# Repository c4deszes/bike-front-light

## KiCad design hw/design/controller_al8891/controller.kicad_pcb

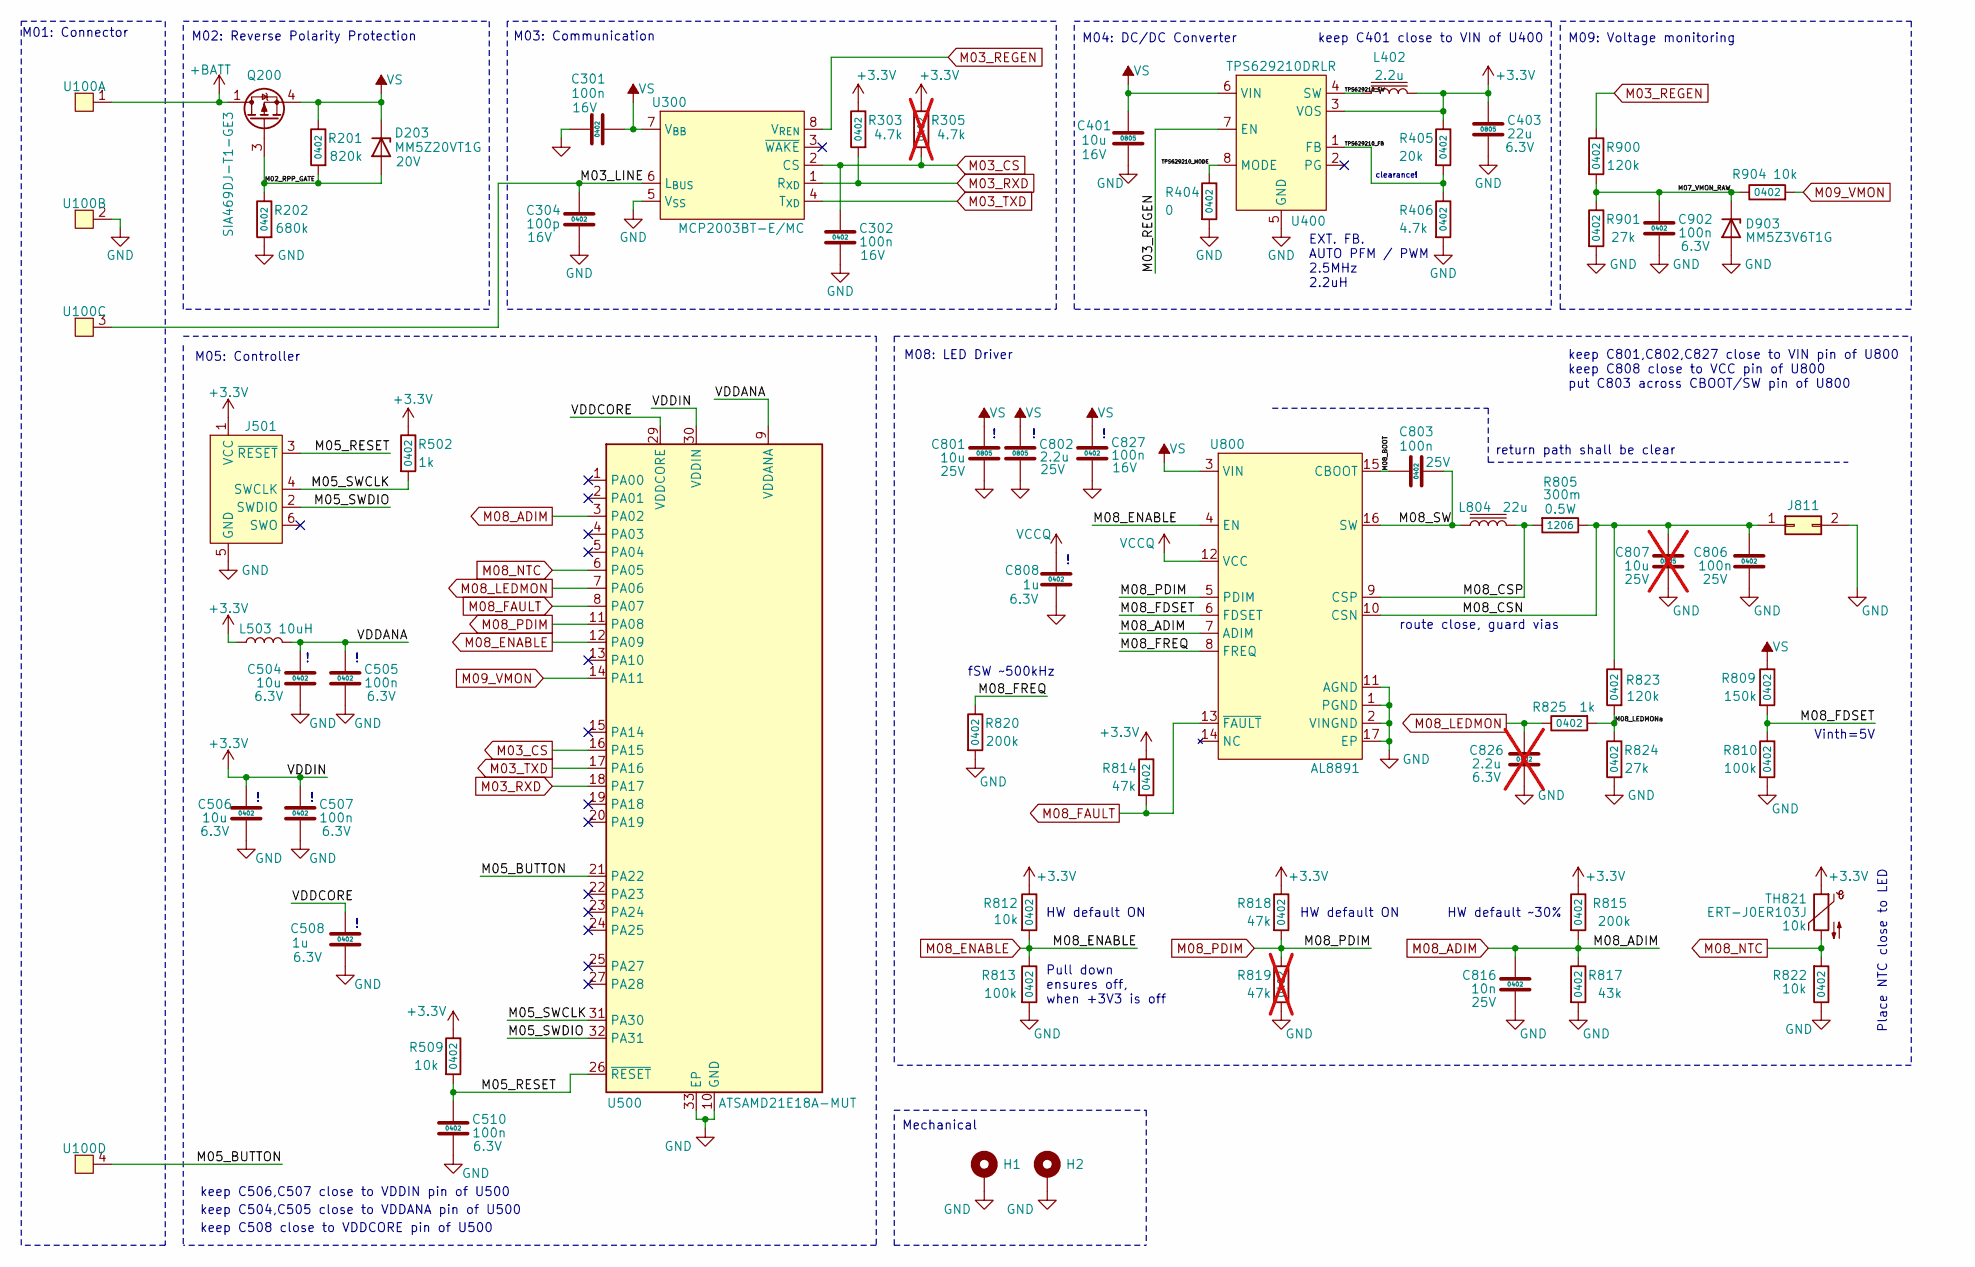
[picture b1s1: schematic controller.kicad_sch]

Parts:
C301, C302, C827: 100n; C_0402_1005Metric; Rating 16V
C304: 100p; C_0402_1005Metric; Rating 16V
C401: 10u; C_0805_2012Metric; Rating 16V
C403: 22u; C_0805_2012Metric; Rating 6.3V
C504, C506: 10u; C_0402_1005Metric; Rating 6.3V
C505, C507, C510, C902: 100n; C_0402_1005Metric; Rating 6.3V
C508, C808: 1u; C_0402_1005Metric; Rating 6.3V
C801: 10u; C_0805_2012Metric; Rating 25V
C802: 2.2u; C_0805_2012Metric; Rating 25V
C803: 100n; C_0603_1608Metric; Rating 25V
C806: 100n; C_0402_1005Metric; Rating 25V
C807: 10u; C_0805_2012Metric; Rating 25V; not fitted
C816: 10n; C_0402_1005Metric; Rating 25V
C826: 2.2u; C_0402_1005Metric; Rating 6.3V; not fitted
D203: MM5Z20VT1G; D_SOD-523; Rating 20V
D903: MM5Z3V6T1G; D_SOD-523
H1, H2: MountingHole_Pad; MountingHole_2.2mm_M2_DIN965_Pad_TopOnly
J501: Conn_ARM_SWD_TagConnect_TC2030-NL; Tag-Connect_TC2030-IDC-NL_2x03_P1.27mm_Vertical
J811: Conn_02x01; 2pinConnector
L402: 2.2u; L_Coilcraft_LPS3010
L503: 10uH; L_0603_1608Metric
L804: 22u; ASPI-6045
Q200: SIA469DJ-T1-GE3; Vishay_PowerPAK_SC70-6L_Single
R201: 820k; R_0402_1005Metric
R202: 680k; R_0402_1005Metric
R303, R406: 4.7k; R_0402_1005Metric
R305: 4.7k; R_0402_1005Metric; not fitted
R404: 0; R_0402_1005Metric
R405: 20k; R_0402_1005Metric
R502, R825: 1k; R_0402_1005Metric
R509, R812, R822, R904: 10k; R_0402_1005Metric
R805: 300m; R_1206_3216Metric; Rating 0.5W
R809: 150k; R_0402_1005Metric
R810, R813: 100k; R_0402_1005Metric
R814, R818: 47k; R_0402_1005Metric
R815, R820: 200k; R_0402_1005Metric
R817: 43k; R_0402_1005Metric
R819: 47k; R_0402_1005Metric; not fitted
R823, R900: 120k; R_0402_1005Metric
R824, R901: 27k; R_0402_1005Metric
TH821: ERT-J0ER103J; R_0402_1005Metric
U100: PinHeader_1x04_P2.54mm_Vertical
U300: MCP2003BT-E/MC; DFN-8-1EP_3x2mm_P0.5mm_EP1.7x1.4mm
U400: TPS629210DRLR; SOT-583-8
U500: ATSAMD21E18A-MUT; VQFN-32-1EP_5x5mm_P0.5mm_EP3.5x3.5mm
U800: AL8891; TSSOP-16-1EP_4.4x5mm_P0.65mm_EP3x3mm

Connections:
+3.3V: C403.1, C506.2, C507.2, J501.1 (VCC), L402.2, L503.1, R303.1, R305.1, R405.1, R502.1, R509.1, R812.1, R814.1, R815.1, R818.1, TH821.1, U400.3 (VOS), U500.30 (VDDIN)
+BATT: Q200.1 (D), U100.1
/M02_RPP_GATE: D203.2 (A), Q200.3 (G), R201.2, R202.1
/M03_LINE: C304.2, U100.3, U300.6 (L_{BUS})
/M05_BUTTON: U100.4, U500.21 (PA22)
/M05_RESET: C510.2, J501.3 (~RESET), R509.2, U500.26 (~RESET)
/M05_SWCLK: J501.4 (SWCLK), R502.2, U500.31 (PA30)
/M05_SWDIO: J501.2 (SWDIO), U500.32 (PA31)
/M07_VMON_RAW: C902.2, D903.1 (K), R900.2, R901.1, R904.1
/M08_BOOT: C803.1, U800.15 (CBOOT)
/M08_CSN: C806.1, C807.2, J811.1, R805.1, R823.1, U800.10 (CSN)
/M08_CSP: L804.2, R805.2, U800.9 (CSP)
/M08_FDSET: R809.2, R810.1, U800.6 (FDSET)
/M08_FREQ: R820.1, U800.8 (FREQ)
/M08_LEDMONa: R823.2, R824.1, R825.2
/M08_SW: C803.2, L804.1, U800.16 (SW)
/TPS629210_FB: R405.2, R406.1, U400.1 (FB)
/TPS629210_MODE: R404.1, U400.8 (MODE)
/TPS629210_SW: L402.1, U400.4 (SW)
/VDDANA: C504.2, C505.2, L503.2, U500.9 (VDDANA)
/VDDCORE: C508.2, U500.29 (VDDCORE)
GND: C301.1, C302.1, C304.1, C401.1, C403.2, C504.1, C505.1, C506.1, C507.1, C508.1, C510.1, C801.1, C802.1, C806.2, C807.1, C808.1, C816.2, C826.1, C827.1, C902.1, D903.2 (A), H1.1, H2.1, J501.5 (GND), J811.2, R202.2, R404.2, R406.2, R810.2, R813.2, R817.2, R819.2, R820.2, R822.1, R824.2, R901.2, U100.2, U300.5 (V_{SS}), U400.5 (GND), U500.10 (GND), U500.28 (GND), U500.33 (EP), U800.1 (PGND), U800.2 (VINGND), U800.11 (AGND), U800.17 (EP)
M03_CS: C302.2, R305.2, U300.2 (CS), U500.16 (PA15)
M03_REGEN: R900.1, U300.8 (V_{REN}), U400.7 (EN)
M03_RXD: R303.2, U300.1 (R_{XD}), U500.18 (PA17)
M03_TXD: U300.4 (T_{XD}), U500.17 (PA16)
M08_ADIM: C816.1, R815.2, R817.1, U500.3 (PA02), U800.7 (ADIM)
M08_ENABLE: R812.2, R813.1, U500.12 (PA09), U800.4 (EN)
M08_FAULT: R814.2, U500.8 (PA07), U800.13 (~FAULT)
M08_LEDMON: C826.2, R825.1, U500.7 (PA06)
M08_NTC: R822.2, TH821.2, U500.6 (PA05)
M08_PDIM: R818.2, R819.1, U500.11 (PA08), U800.5 (PDIM)
M09_VMON: R904.2, U500.14 (PA11)
VCCQ: C808.2, U800.12 (VCC)
VS: C301.2, C401.2, C801.2, C802.2, C827.2, D203.1 (K), Q200.4 (S), R201.1, R809.1, U300.7 (V_{BB}), U400.6 (VIN), U800.3 (VIN)

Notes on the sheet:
route close, guard vias
Pull down ensures off, when +3V3 is off
M09: Voltage monitoring
M04: DC/DC Converter
EXT. FB. AUTO PFM / PWM 2.5MHz 2.2uH
return path shall be clear
keep C504,C505 close to VDDANA pin of U500
M02: Reverse Polarity Protection
keep C801,C802,C827 close to VIN pin of U800 keep C808 close to VCC pin of U800 put C803 across CBOOT/SW pin of U800
keep C508 close to VDDCORE pin of U500
HW default ON
clearance!
Mechanical
keep C506,C507 close to VDDIN pin of U500
Place NTC close to LED
M05: Controller
M03: Communication
M01: Connector
Vinth=5V
keep C401 close to VIN of U400
HW default ~30%
M08: LED Driver
fSW ~500kHz

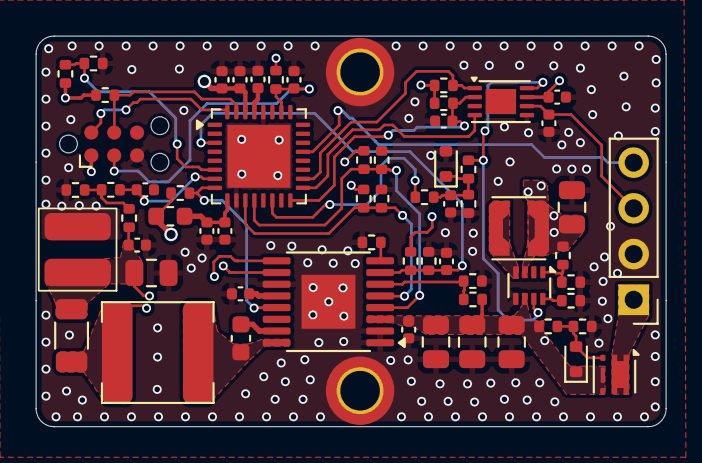
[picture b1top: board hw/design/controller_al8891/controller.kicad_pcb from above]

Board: 4 copper layers, 35.0 x 21.7 mm, 64 parts (0 on the bottom side), 35 nets.

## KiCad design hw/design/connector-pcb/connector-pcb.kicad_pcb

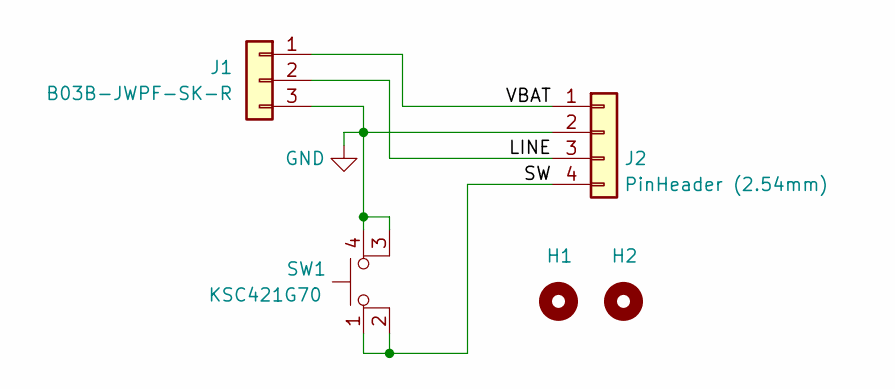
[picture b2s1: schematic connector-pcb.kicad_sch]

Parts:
H1, H2: MountingHole_Pad; MountingHole_2.2mm_M2_ISO14580
J1: B03B-JWPF-SK-R; JST_JWPF_B03B-JWPF-SK-R_1x03_P2.00mm_Vertical
J2: PinHeader (2.54mm); PinHeader_1x04_P2.00mm_Vertical_SMD_Pin1Left
SW1: KSC421G70; KSC4

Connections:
/LINE: J1.2, J2.3
/SW: J2.4, SW1.1, SW1.2
/VBAT: J1.1, J2.1
GND: J1.3, J2.2, SW1.3 (K), SW1.4 (A)

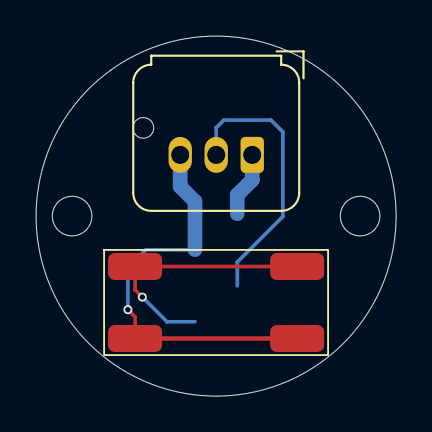
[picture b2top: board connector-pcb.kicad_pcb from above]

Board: 2 copper layers, 20.0 x 20.0 mm, 5 parts (1 on the bottom side), 4 nets.

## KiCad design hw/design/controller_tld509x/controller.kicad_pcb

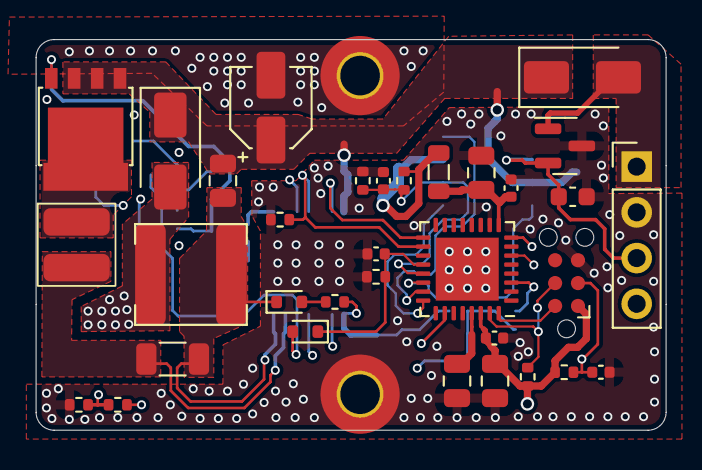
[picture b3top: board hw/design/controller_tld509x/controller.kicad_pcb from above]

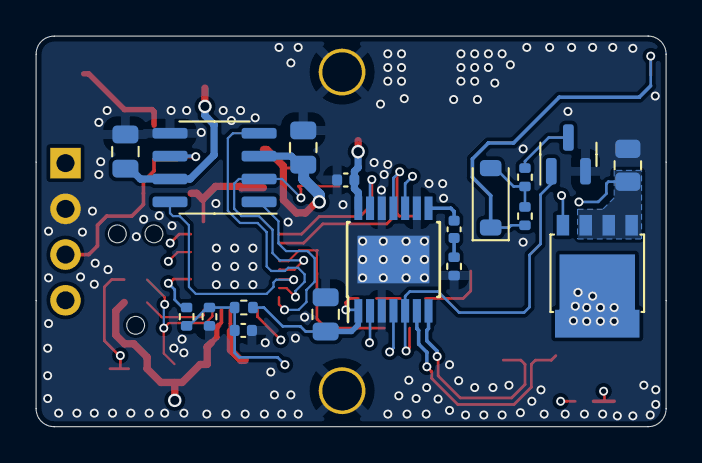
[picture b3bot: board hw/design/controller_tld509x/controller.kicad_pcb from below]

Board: 4 copper layers, 35.0 x 21.7 mm, 53 parts (18 on the bottom side), 35 nets.

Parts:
C300, C401, C403, C502: 10u; C_0805_2012Metric
C301: 22u; C_0805_2012Metric
C302: 220p; C_0603_1608Metric
C303, C400, C402, C404, C501, C504, C506: 100n; C_0402_1005Metric
C405, C503: 2.2u; C_0805_2012Metric
C500: 100u; CP_Elec_4x5.3
C505: 22n; C_0402_1005Metric
D200, D500: SS34F-DC; D_SMA
D300: SDT23C15L02; SOT-23
D501, D502: BAS3005B02; D_SOD-523
D503: BZT52C20-TP; D_SOD-123
H1, H2: M2; MountingHole_2.2mm_M2_Pad_TopOnly
J400: Conn_ARM_SWD_TagConnect_TC2030-NL; Tag-Connect_TC2030-IDC-NL_2x03_P1.27mm_Vertical
J500: Conn_02x01; 2pinConnector
L400: 10uH; L_0805_2012Metric
L500: 15u; ASPI-6045
Q500: BUK6Y24-40PX; LFPAK56
Q501: BUK7Y7R0-40HX; LFPAK56
Q502: 2N7002; SOT-23
R300, R301, R401, R402, R502, R507, R509, R510: 10k; R_0402_1005Metric
R400: 1k; R_0402_1005Metric
R500: 0.430; R_1206_3216Metric
R501: 50m; R_0805_2012Metric
R503, R504, R505, R508: 20k; R_0402_1005Metric
R506: 4.7k; R_0402_1005Metric
TH400: ERT-J0ER103J; R_0402_1005Metric
U100: PinHeader_1x04_P2.54mm_Vertical
U300: MCP2021A-500E/SN; SOIC-8_3.9x4.9mm_P1.27mm
U400: ATSAMC21E18A-MNT; VQFN-32-1EP_5x5mm_P0.5mm_EP3.5x3.5mm
U500: TLD509x; Infineon_PG-TSDSO-14-22

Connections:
+3.3V: C301.1, C403.2, C404.2, J400.1 (VCC), L400.1, R300.1, R400.1, R401.1, TH400.1, U300.3 (VREG), U400.30 (VDDIN)
+BATT: C300.2, C500.1, C501.2, C502.2, D200.1 (K), D500.1 (K), Q500.1 (S), Q500.2 (S), Q500.3 (S), U300.7 (VBB), U500.14 (IN)
/M03_CS: C303.2, R300.2, R301.1, U300.2 (CS/LWAKE), U400.21 (PA22)
/M03_LINE: C302.1, D300.2 (K), U100.3, U300.6 (LBUS)
/M03_RXD: U300.1 (RXD), U400.24 (PA25)
/M03_TXD: U300.4 (TXD), U400.23 (PA24)
/M03_TXE: U300.8 (~FAULT/TXE), U400.22 (PA23)
/M05_BUTTON: U100.4, U400.8 (PA07)
/M05_FAULT: C506.2, D502.1 (K), R508.1, U400.20 (PA19)
/M05_FREQ: R506.1, U400.18 (PA17), U500.11 (FREQ/SYNC)
/M05_ISET: R505.1, U400.3 (PA02)
/M05_NTC: R402.2, TH400.2, U400.6 (PA05)
/M05_PWMI: U400.17 (PA16), U500.13 (EN/PWMI)
/M05_RESET: C400.2, J400.3 (~RESET), R401.2, U400.26 (~RESET)
/M05_SWCLK: J400.4 (SWCLK), R400.2, U400.31 (PA30)
/M05_SWDIO: J400.2 (SWDIO), U400.32 (PA31)
/TLD509x_COMP: C505.1, U500.8 (COMP)
/TLD509x_CS: Q501.1 (S), Q501.2 (S), Q501.3 (S), R501.2, U500.4 (SWCS)
/TLD509x_FB_N: C502.1, D501.1 (K), L500.1, R500.2, U500.7 (FBL)
/TLD509x_FB_P: J500.2, R500.1, U500.6 (FBH)
/TLD509x_LH: J500.1, Q500.5 (D)
/TLD509x_LL: D500.2 (A), L500.2, Q501.5 (D)
/TLD509x_Ngate: Q501.4 (G), U500.2 (SWO)
/TLD509x_PWMO: D502.2 (A), Q502.1 (G), U500.5 (ST/PWMO)
/TLD509x_Pgate: D503.1 (K), Q500.4 (G), R509.1
/TLD509x_SET: C504.2, R503.1, R504.2, R505.2, U500.10 (SET)
/VDDANA: C401.2, C402.2, L400.2, U400.9 (VDDANA)
/VDDCORE: C405.2, U400.29 (VDDCORE)
GND: C300.1, C301.2, C302.2, C303.1, C400.1, C401.1, C402.1, C403.1, C404.1, C405.1, C500.2, C501.1, C503.1, C504.1, C506.1, D300.3 (A), H1.1, H2.1, J400.5 (GND), Q502.2 (S), R301.2, R402.1, R501.1, R504.1, R506.2, R507.2, R508.2, U100.2, U300.5 (VSS), U400.10 (GND), U400.28 (GND), U400.33 (EP), U500.3 (SGND/FPWM), U500.9 (OVFB), U500.12 (GND), U500.15 (EP)
unnamed: C505.2, R507.1
unnamed: D501.2 (A), R502.2
unnamed: D503.2 (A), R509.2, R510.1
unnamed: Q502.3 (D), R510.2
VCCQ: C503.2, R502.1, R503.2, U500.1 (IVCC)
VS: D200.2 (A), D300.1 (K), U100.1

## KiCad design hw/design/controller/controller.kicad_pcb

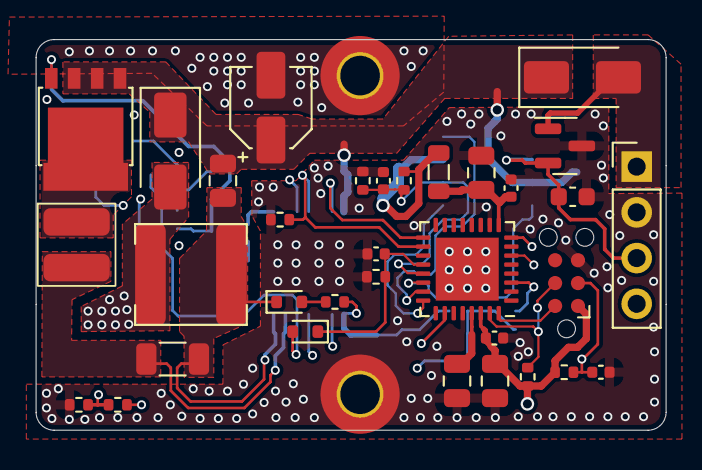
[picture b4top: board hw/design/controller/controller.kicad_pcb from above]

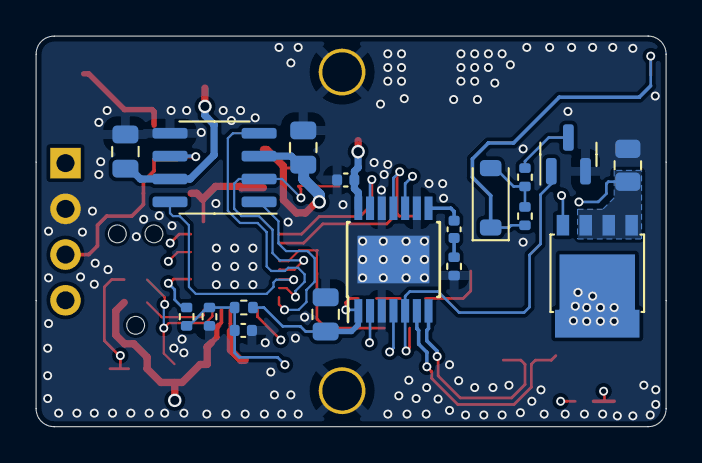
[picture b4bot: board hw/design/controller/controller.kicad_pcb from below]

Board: 4 copper layers, 35.0 x 21.7 mm, 53 parts (18 on the bottom side), 35 nets.

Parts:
C1, C6, C13: 10u; C_0805_2012Metric
C2, C7, C9, C15: 100n; C_0402_1005Metric
C4, C20: 220n; C_0402_1005Metric
C8, C18: 2.2u; C_0805_2012Metric
C12: 220p; C_0603_1608Metric
C14: 22u; C_0805_2012Metric
C17: 100u; CP_Elec_4x5.3
C19, C22: 47n; C_0402_1005Metric
C21: 4.7u; C_0805_2012Metric
D1: BZT52C20-TP; D_SOD-123
D3: SDT23C15L02; SOT-23
D5, D6: BAS3005B02; D_SOD-523
D7, D8: SS34F-DC; D_SMA
H1, H2: M2; MountingHole_2.2mm_M2_Pad_TopOnly
J1: Conn_ARM_SWD_TagConnect_TC2030-NL; Tag-Connect_TC2030-IDC-NL_2x03_P1.27mm_Vertical
J3: Conn_02x01; 2pinConnector
L1: 10uH; L_0805_2012Metric
L2: 15u; ASPI-6045
Q1: PSMN5R2-60YL; LFPAK56
Q3: 2N7002; SOT-23
Q5: SiSS27DN; LFPAK56
R1: 1k; R_0402_1005Metric
R2, R3, R4, R5, R6, R12, R13, R14: 10k; R_0402_1005Metric
R8, R9, R10, R11, R16: 20k; R_0402_1005Metric
R15: 0.430; R_1206_3216Metric
R17: 50m; R_0805_2012Metric
TH1: ERT-J0ER103J; R_0402_1005Metric
U1: ATSAMC21E18A-MNT; VQFN-32-1EP_5x5mm_P0.5mm_EP3.5x3.5mm
U2: TLD509x; Infineon_PG-TSDSO-14-22
U4: MCP2021A-330E/SN; SOIC-8_3.9x4.9mm_P1.27mm
U5: PinHeader_1x04_P2.54mm_Vertical

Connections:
+3.3V: C1.2, C4.2, C14.1, J1.1 (VCC), L1.1, R1.1, R2.1, R5.1, TH1.1, U1.30 (VDDIN), U4.3 (VREG)
+BATT: C2.2, C13.2, C17.1, C21.2, D7.1 (K), D8.1 (K), Q5.1 (S), Q5.2 (S), Q5.3 (S), U2.14 (IN), U4.7 (VBB)
/M03_CS: C15.2, R4.1, R5.2, U1.21 (PA22), U4.2 (CS/LWAKE)
/M03_LINE: C12.1, D3.2 (K), U4.6 (LBUS), U5.3
/M03_RXD: U1.24 (PA25), U4.1 (RXD)
/M03_TXD: U1.23 (PA24), U4.4 (TXD)
/M03_TXE: U1.22 (PA23), U4.8 (~FAULT/TXE)
/M05_BUTTON: U1.8 (PA07), U5.4
/M05_FAULT: C22.2, D5.1 (K), R16.1, U1.20 (PA19)
/M05_FREQ: R8.1, U1.18 (PA17), U2.11 (FREQ/SYNC)
/M05_ISET: R9.1, U1.3 (PA02)
/M05_NTC: R3.2, TH1.2, U1.6 (PA05)
/M05_PWMI: U1.17 (PA16), U2.13 (EN/PWMI)
/M05_RESET: C9.2, J1.3 (~RESET), R2.2, U1.26 (~RESET)
/M05_SWCLK: J1.4 (SWCLK), R1.2, U1.31 (PA30)
/M05_SWDIO: J1.2 (SWDIO), U1.32 (PA31)
/TLD509x_COMP: C19.1, U2.8 (COMP)
/TLD509x_CS: Q1.1 (S), Q1.2 (S), Q1.3 (S), R17.2, U2.4 (SWCS)
/TLD509x_FB_N: C21.1, D6.1 (K), L2.1, R15.2, U2.7 (FBL)
/TLD509x_FB_P: J3.2, R15.1, U2.6 (FBH)
/TLD509x_LH: J3.1, Q5.5 (D)
/TLD509x_LL: D7.2 (A), L2.2, Q1.5 (D)
/TLD509x_Ngate: Q1.4 (G), U2.2 (SWO)
/TLD509x_PWMO: D5.2 (A), Q3.1 (G), U2.5 (ST/PWMO)
/TLD509x_Pgate: D1.1 (K), Q5.4 (G), R12.1
/TLD509x_SET: C20.2, R9.2, R10.1, R11.2, U2.10 (SET)
/VDDANA: C6.2, C7.2, L1.2, U1.9 (VDDANA)
/VDDCORE: C8.2, U1.29 (VDDCORE)
GND: C1.1, C2.1, C4.1, C6.1, C7.1, C8.1, C9.1, C12.2, C13.1, C14.2, C15.1, C17.2, C18.1, C20.1, C22.1, D3.3 (A), H1.1, H2.1, J1.5 (GND), Q3.2 (S), R3.1, R4.2, R6.2, R8.2, R11.1, R16.2, R17.1, U1.10 (GND), U1.28 (GND), U1.33 (EP), U2.3 (SGND/FPWM), U2.9 (OVFB), U2.12 (GND), U2.15 (EP), U4.5 (VSS), U5.2
unnamed: C19.2, R6.1
unnamed: D1.2 (A), R12.2, R13.1
unnamed: D6.2 (A), R14.2
unnamed: Q3.3 (D), R13.2
VCCQ: C18.2, R10.2, R14.1, U2.1 (IVCC)
VS: D3.1 (K), D8.2 (A), U5.1

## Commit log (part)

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2024-05-25 Initial hardware design
2024-05-28 Final hardware design
2024-06-09 Initial software
2024-06-11 Temperature monitoring (not working)
2024-06-22 Hardware schematic cleanup
2024-06-22 Button controlled software
2024-06-23 New network.json
2024-06-23 Mechanical model
2024-08-13 Working remote control and button feedback
2024-08-14 Fixed temperature measurement
2024-08-15 ILD8150 voltage monitoring (not working)
2024-08-16 TLD509x analog control support
2025-01-21 New software parameters
2025-01-21 Connector board modified to use the 3pin connector
2025-10-22 Updating to latest LINE library version
2025-10-22 Latest LINE lib
2025-10-22 Test cases
2025-10-22 Flash script
2025-10-22 Documentation
2025-10-22 Latest network spec.
2025-10-22 Gen1.1 mechanical design
    Reduces number of parts, instead of pressfit ring it's
    an oring seal that keeps the assembly inside the case.
    The new button cover should provide better ingress
    protection.
    The new internal carrier is slightly shorter and has an
    oring to seal some of the electronics.
2026-05-10 Complete Gen1.1 based on AL8891
2026-05-21 Finalized design (JLC ordered)
